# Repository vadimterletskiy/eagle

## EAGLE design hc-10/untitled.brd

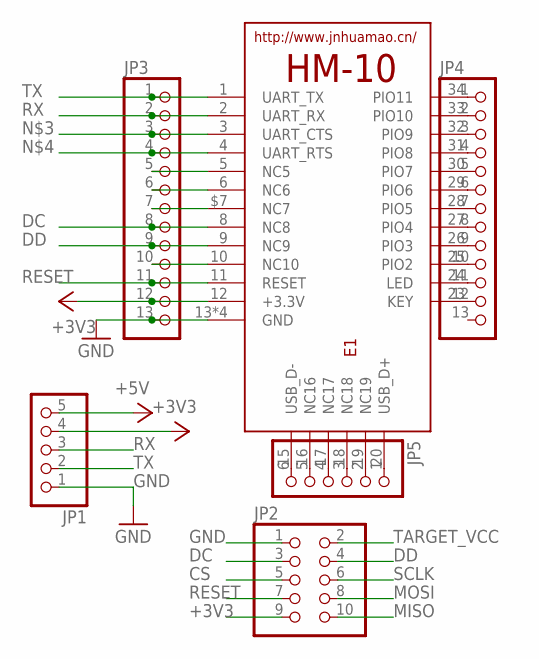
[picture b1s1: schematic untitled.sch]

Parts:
E1: HM-10-BOARD; 26.9X13X2.2_BOARD
JP1: PINHD-1X5; 1X05
JP2: PINHD-2X5; 2X05
JP3, JP4: PINHD-1X13; 1X13
JP5: PINHD-1X6; 1X06

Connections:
+3V3: E1.12 (+3.3V), JP1.4, JP2.9, JP3.12
+5V: JP1.5
CS: JP2.5
DC: E1.8 (NC8), JP2.3, JP3.8
DD: E1.9 (NC9), JP2.4, JP3.9
GND: E1.13 (GND), E1.14 (GND), E1.21 (GND), E1.22 (GND), JP1.1, JP2.1, JP3.13
MISO: JP2.10
MOSI: JP2.8
unnamed: E1.5 (NC5), JP3.5
unnamed: E1.6 (NC6), JP3.6
unnamed: E1.3 (UART_CTS), JP3.3
unnamed: E1.4 (UART_RTS), JP3.4
unnamed: E1.$7 (NC7), JP3.7
unnamed: E1.10 (NC10), JP3.10
unnamed: E1.34 (PIO11), JP4.1
unnamed: E1.33 (PIO10), JP4.2
unnamed: E1.32 (PIO9), JP4.3
unnamed: E1.31 (PIO8), JP4.4
unnamed: E1.30 (PIO7), JP4.5
unnamed: E1.29 (PIO6), JP4.6
unnamed: E1.28 (PIO5), JP4.7
unnamed: E1.27 (PIO4), JP4.8
unnamed: E1.26 (PIO3), JP4.9
unnamed: E1.25 (PIO2), JP4.10
unnamed: E1.24 (LED), JP4.11
unnamed: E1.23 (KEY), JP4.12
unnamed: E1.20 (USB_D+), JP5.1
unnamed: E1.19 (NC19), JP5.2
unnamed: E1.18 (NC18), JP5.3
unnamed: E1.17 (NC17), JP5.4
unnamed: E1.16 (NC16), JP5.5
unnamed: E1.15 (USB_D-), JP5.6
RESET: E1.11 (RESET), JP2.7, JP3.11
RX: E1.2 (UART_RX), JP1.3, JP3.2
SCLK: JP2.6
TARGET_VCC: JP2.2
TX: E1.1 (UART_TX), JP1.2, JP3.1

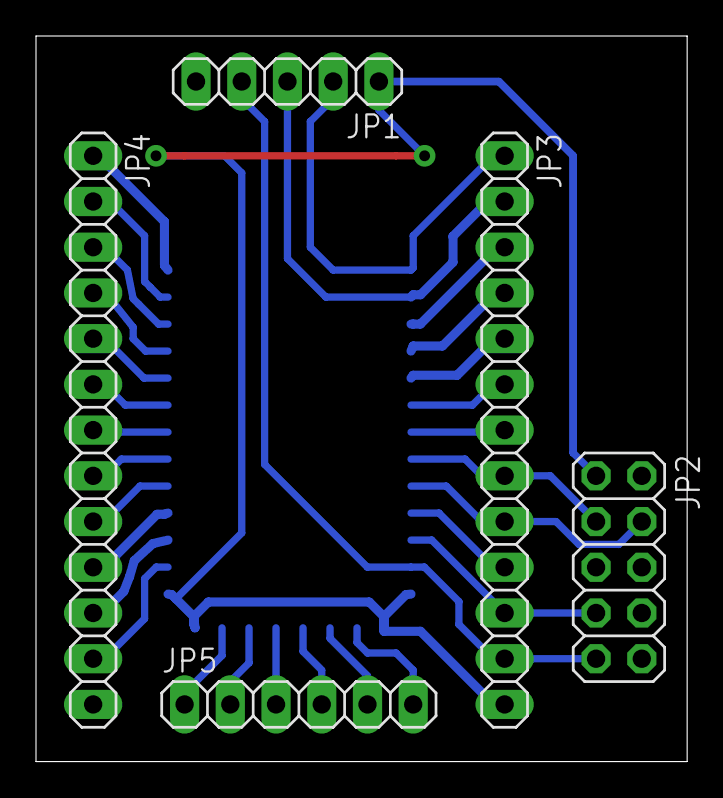
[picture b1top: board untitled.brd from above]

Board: 2 copper layers, 36.2 x 40.3 mm, 6 parts (1 on the bottom side), 31 nets.

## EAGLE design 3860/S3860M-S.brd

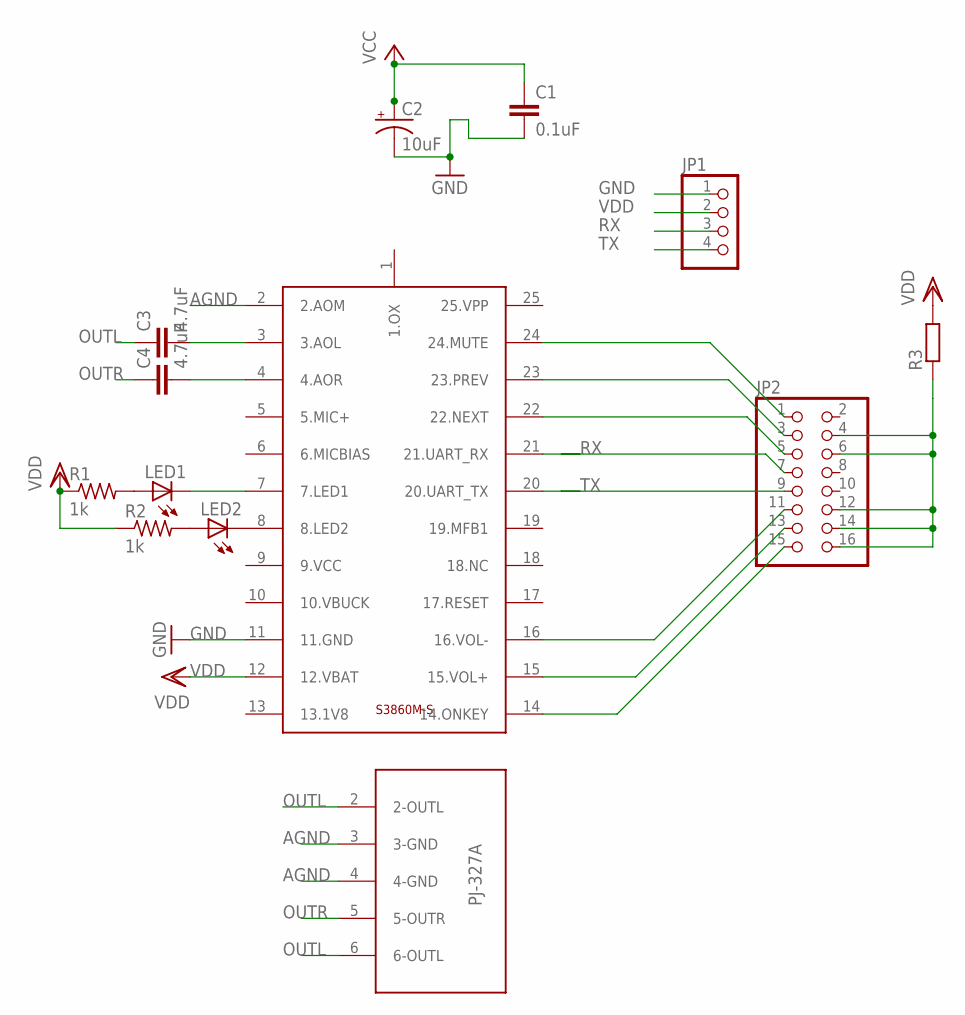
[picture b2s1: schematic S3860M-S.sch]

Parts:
C1: 0.1uF; 1206
C2: 10uF; PANASONIC_E
C3, C4: 4.7uF; C1206
JP1: PINHD-1X4; 1X04
JP2: PINHD-2X8; 2X08
LED1, LED2: LEDCHIPLED_0805; CHIPLED_0805
R1, R2: 1k; R1206
R3: R-EU_M1206; M1206
U$1: S3860M-S
U$2: PJ-327A

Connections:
AGND: U$1.2 (2.AOM), U$2.3 (3-GND), U$2.4 (4-GND)
GND: C1.2, C2.-, JP1.1, U$1.11 (11.GND)
unnamed: LED2.A, R2.2
unnamed: JP2.15, U$1.14 (14.ONKEY)
unnamed: LED1.C, U$1.7 (7.LED1)
unnamed: LED2.C, U$1.8 (8.LED2)
unnamed: LED1.A, R1.2
unnamed: JP2.13, U$1.15 (15.VOL+)
unnamed: JP2.11, U$1.16 (16.VOL-)
unnamed: JP2.1, U$1.24 (24.MUTE)
unnamed: JP2.3, U$1.23 (23.PREV)
unnamed: C4.2, U$1.4 (4.AOR)
unnamed: C3.2, U$1.3 (3.AOL)
unnamed: JP2.5, U$1.22 (22.NEXT)
unnamed: JP2.4, JP2.6, JP2.12, JP2.14, JP2.16, R3.1
OUTL: C3.1, U$2.2 (2-OUTL), U$2.6 (6-OUTL)
OUTR: C4.1, U$2.5 (5-OUTR)
RX: JP1.3, JP2.7, U$1.21 (21.UART_RX)
TX: JP1.4, JP2.9, U$1.20 (20.UART_TX)
VCC: C1.1, C2.+
VDD: JP1.2, R1.1, R2.1, R3.2, U$1.12 (12.VBAT)

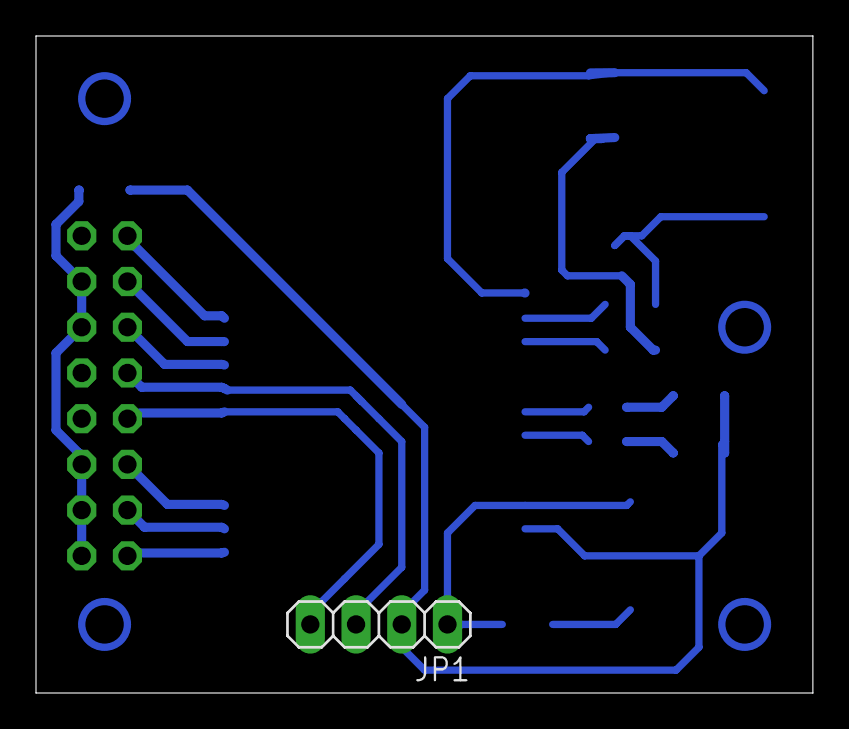
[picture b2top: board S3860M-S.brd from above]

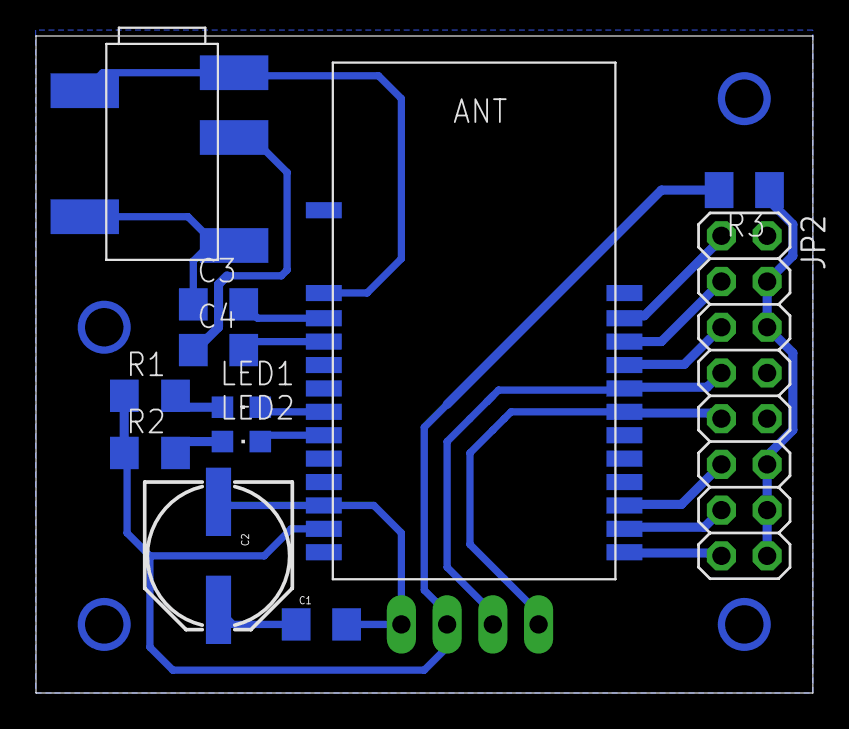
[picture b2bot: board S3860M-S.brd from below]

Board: 2 copper layers, 43.2 x 36.5 mm, 13 parts (12 on the bottom side), 21 nets.

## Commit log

2015-10-02 3860 BT audio
2015-10-02 ble hc-10

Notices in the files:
parts and their libraries:
SparkFun-Capacitors: Licensing: CC v3.0 Share-Alike You are welcome to use this library for commercial purposes.
